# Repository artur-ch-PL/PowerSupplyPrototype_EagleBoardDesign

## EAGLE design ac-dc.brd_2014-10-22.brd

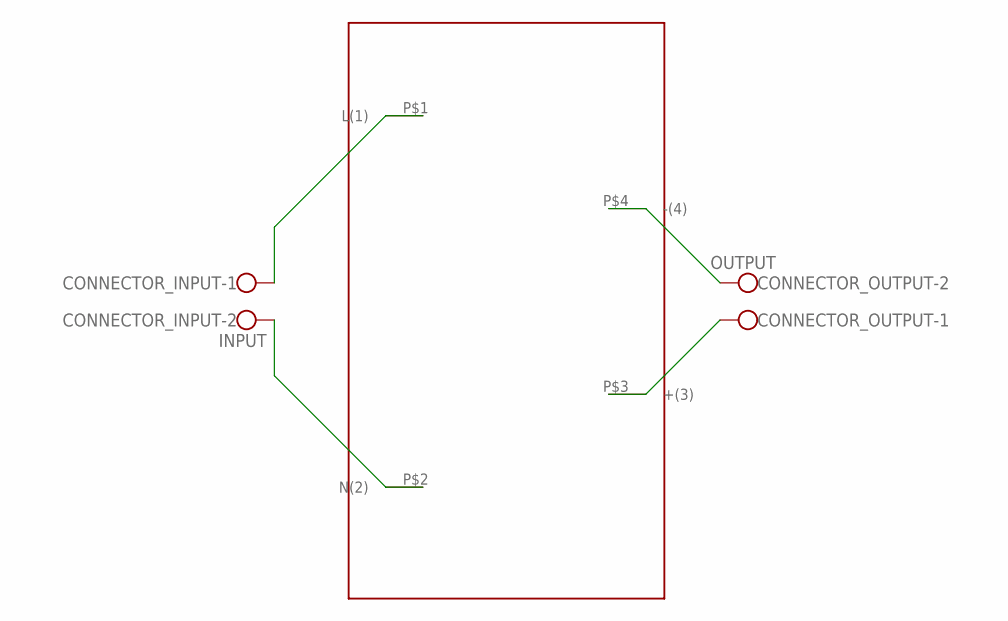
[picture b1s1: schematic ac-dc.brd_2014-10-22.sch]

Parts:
CONNECTOR_INPUT: INPUT; W237-102
CONNECTOR_OUTPUT: OUTPUT; W237-102
U$2: VTX_214; VTX-214-005

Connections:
unnamed: CONNECTOR_OUTPUT.2, U$2.P$4 (-(4))
unnamed: CONNECTOR_OUTPUT.1, U$2.P$3 (+(3))
unnamed: CONNECTOR_INPUT.2, U$2.P$2 (N(2))
unnamed: CONNECTOR_INPUT.1, U$2.P$1 (L(1))

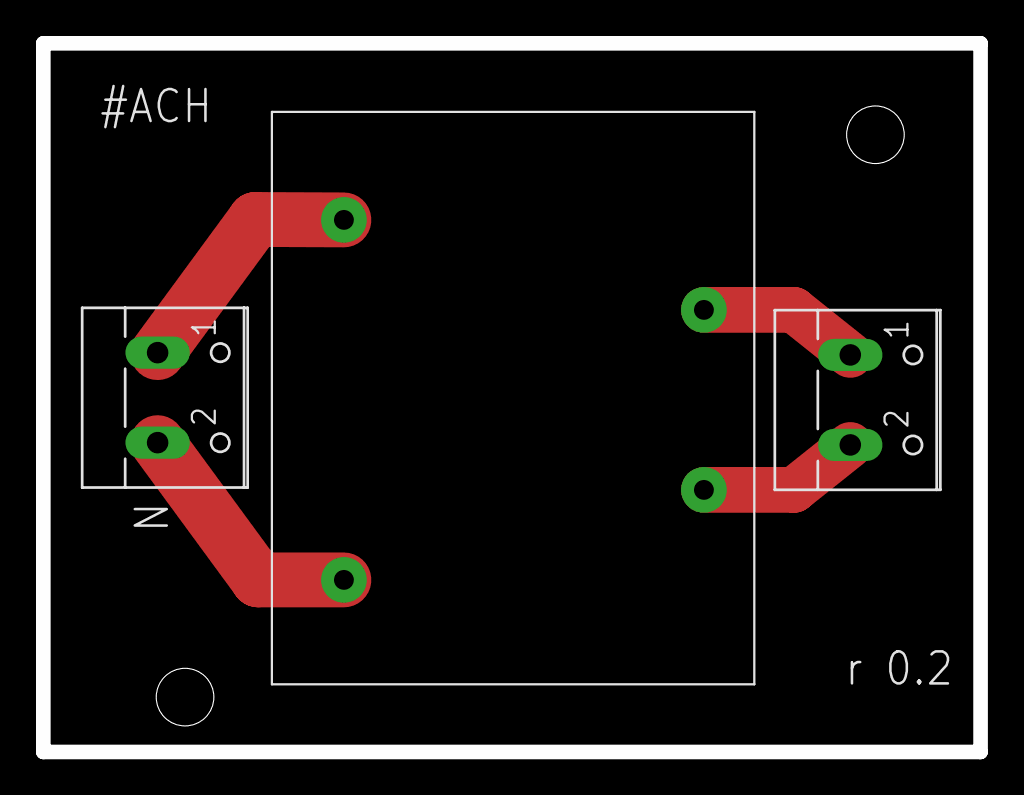
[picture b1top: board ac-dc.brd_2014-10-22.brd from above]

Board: 2 copper layers, 52.1 x 39.4 mm, 3 parts (0 on the bottom side), 4 nets.

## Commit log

2014-12-01 initil commit
